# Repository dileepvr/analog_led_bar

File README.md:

This PCB schematic and layout is being released under the CERN Open
Hardware License v1.2. All future versions of the CERN Open Hardware
License automatically apply. View the file LICENSE.txt for more
information.

Here is a simple schematic (and BOM) for a circuit that uses 20 leds
(10 for positive and 10 for negative) to indicate the value of an
analog voltage set to a midpoint reference. A potentiometer sets
sensitivity, and an onboard surface mount resistor sets brightness.

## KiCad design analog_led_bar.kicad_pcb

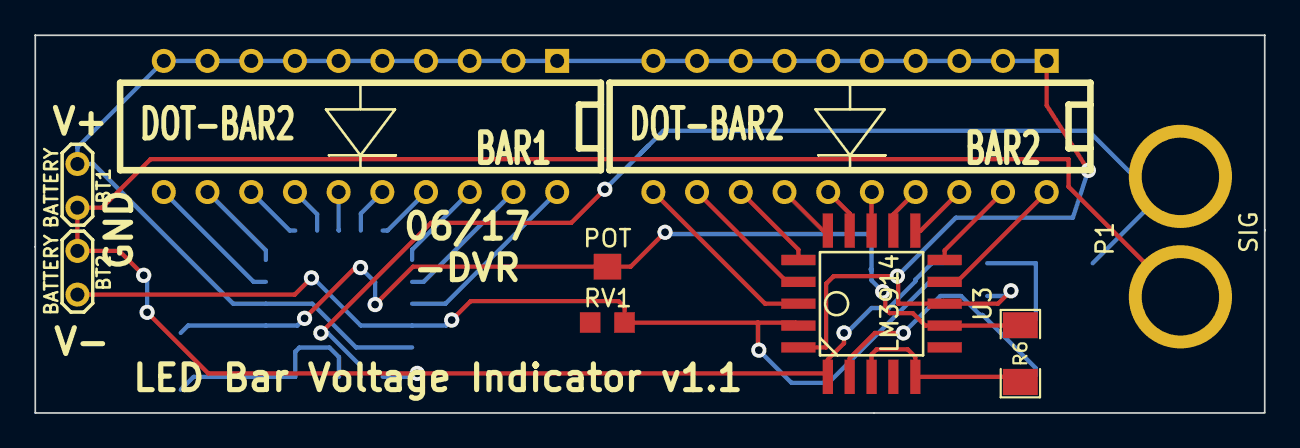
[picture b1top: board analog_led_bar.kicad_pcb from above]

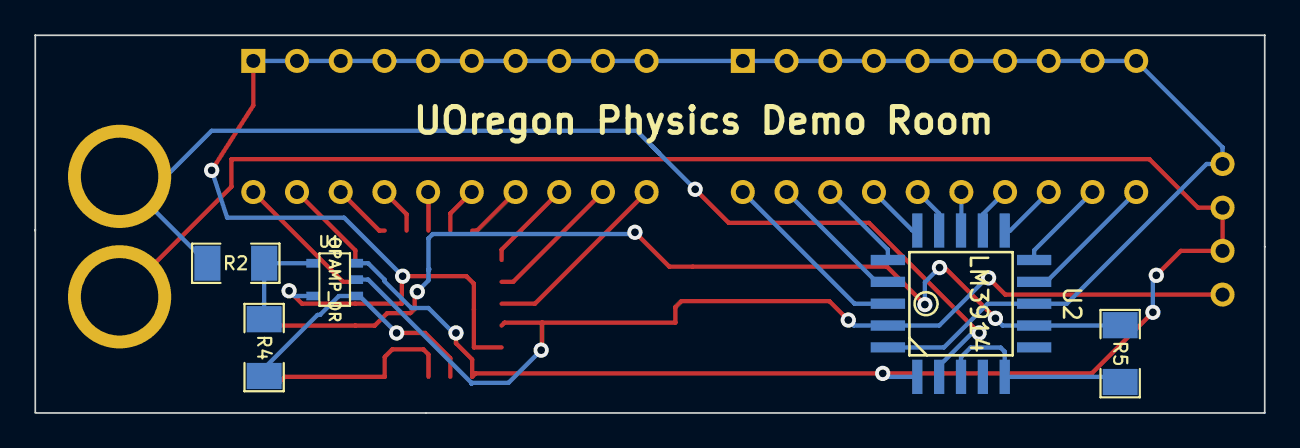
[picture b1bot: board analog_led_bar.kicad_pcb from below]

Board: 2 copper layers, 71.4 x 22.0 mm, 13 parts (5 on the bottom side), 29 nets.

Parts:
BAR1, BAR2: DOT-BAR2; 10_LED_BAR
BT1, BT2: BATTERY; BATT
P1: SIG; TEST_PLUGS
R2, R4: 1K; SM1206
R5, R6: 1.2K; SM1206
RV1: POT; TC33X-2
U1: OPAMP_DR; SOT23-5
U2, U3: LM3914; S-PQCC-J20

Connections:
/ADJ: R5.2, R6.2, RV1.2, U2.10, U3.10
/GL1: BAR2.11, U3.1
/GL2: BAR2.12, U3.20
/GL3: BAR2.13, U3.19
/GL4: BAR2.14, U3.18
/GL5: BAR2.15, U3.17
/GL6: BAR2.16, U3.16
/GL7: BAR2.17, U3.15
/GL8: BAR2.18, U3.14
/GL9: BAR2.19, U3.13
/GL10: BAR2.20, U3.12
/GND: BT2.2, RV1.3, U1.2, U2.2, U3.2
/RL1: BAR1.20, U2.1
/RL2: BAR1.19, U2.20
/RL3: BAR1.18, U2.19
/RL4: BAR1.17, U2.18
/RL5: BAR1.16, U2.17
/RL6: BAR1.15, U2.16
/RL7: BAR1.14, U2.15
/RL8: BAR1.13, U2.14
/RL9: BAR1.12, U2.13
/RL10: BAR1.11, U2.12
/SIG+: P1.2, R2.2, U2.5
/SIG-: R4.1, U1.1, U3.5
/Vcc: BAR1.1, BAR1.2, BAR1.3, BAR1.4, BAR1.5, BAR1.6, BAR1.7, BAR1.8, BAR1.9, BAR1.10, BAR2.1, BAR2.2, BAR2.3, BAR2.4, BAR2.5, BAR2.6, BAR2.7, BAR2.8, BAR2.9, BAR2.10, BT1.1, U1.5, U2.3, U2.11, U3.3, U3.11
/Vmid: BT1.2, BT2.1, P1.1, U1.3, U2.4, U3.4
unnamed: R5.1, U2.6, U2.8
unnamed: R2.1, R4.2, U1.4
unnamed: R6.1, U3.6, U3.8

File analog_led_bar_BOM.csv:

Part,Qty.,Schematic names,Description,Mouser link:
RK73H2BTTD1001F,2,"R2, R4",SM1206 resistors (1K),http://www.mouser.com/ProductDetail/KOA-Speer/RK73H2BTTD1001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
RK73H2BTTD1201F,2,"R5, R6",SM1206 resistors (1.2K),http://www.mouser.com/ProductDetail/KOA-Speer/RK73H2BTTD1201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
TC33X-2-103E,1,RV1,Trimmer Resistor (10K),http://www.mouser.com/ProductDetail/Bourns/TC33X-2-103E/?qs=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
651-0303312,2,P1,Banana plug receptacles,http://www.mouser.com/ProductDetail/Phoenix-Contact/0303312/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
DC10GWA,1,BAR1,10 LED green array,http://www.mouser.com/ProductDetail/Kingbright/DC10GWA/?qs=s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
DC10SRWA,1,BAR2,10 LED red array,http://www.mouser.com/ProductDetail/Kingbright/DC10SRWA/?qs=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
LM3914VX/NOPB,2,"U2, U3",TI LED driver ICs (S-PQCC-J20),http://www.mouser.com/ProductDetail/Texas-Instruments/LM3914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
TLV8811DBVR,1,U1,SOT-23-5 OpAmp,http://www.mouser.com/ProductDetail/Texas-Instruments/TLV881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

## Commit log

2016-07-30 Project finished.
2016-07-30 Added LICENSE and README.
2017-06-15 Fixed unconnected nodes. Now v1.1. Confirmed works if variable resistor is set properly.
2017-06-15 BOM added.
